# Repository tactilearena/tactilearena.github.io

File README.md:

# TactileArena

**Scalable high-density tactile arenas for measuring ground-contact forces in freely moving animals**
Weiwen Lu\*, Ariel Slepyan\*, Pierce Perkins, Alessandro Ascani Orsini, Kiara Quinn, Nitish V. Thakor (\*equal contribution).
Johns Hopkins University and MIT. Preprint: [bioRxiv](https://www.biorxiv.org/content/10.64898/2026.10.22.760735v1) (2026).

**Website: <https://tactilearena.github.io>** · [Preprint](https://www.biorxiv.org/content/10.64898/2026.10.22.760735v1) · [How it works](https://tactilearena.github.io/how-it-works/) · [Build guide](https://tactilearena.github.io/build/) · [Data](https://tactilearena.github.io/data/)

TactileArena transforms the floor into a sensor. A modular surface of 16,384 pressure-sensitive taxels (2-mm pitch, 512 × 128 mm, nominal 1 kHz) records where, when and with what force a freely moving animal contacts the ground, synchronized with overhead video and without instrumentation of the animal. Each readout board measures 200 of its module's 4,096 taxels per frame and concentrates these measurements on active contacts (adaptive compressive sampling), enabling this combination of sensing area, spatial density and acquisition speed.

The runway is a 64 × 256 piezoresistive array (four 64 × 64 modules, each with its own readout board) under a walking surface, recorded together with an overhead camera and a side camera. This repository holds the readout firmware, the synchronized recording code, the pipeline that takes each recording from raw sensor packets to paw-labeled (FL/FR/HL/HR) stance events and mass-equivalent loading, and the project website (`docs/`).

## Repository layout

```
acquisition/   record_runway.py         four boards + overhead and side cameras on one clock -> .mat + .mp4
               live_view_runway.py      live pressure map (no recording)
               firmware/                readout-board firmware (Teensy 4.1; set BOARD_ID per board)
pipeline/      gait_config.m            paths and study settings (edit this first)
               s1_prepare_recordings.m  background models; video choice and platform corners for new data
               s2_detect_contacts.m     tail-base CNN + contact detector -> pressure movie, contacts
               peak_seed_contact_detector.m  the contact detector (called by s2)
               s3_find_mobile_bouts.m   whole-animal COP trace and walking bouts (+ review window)
               s4_label_paws.m          FL/FR/HL/HR stance events inside the walking bouts (+ labeled video)
               s5_calibrate_to_grams.m  summed taxel response -> mass-equivalent grams
tailbase/      tailbase_cnn.py          tail-base localizer: annotate / train / predict
demo/          run_demo.m               runs the pipeline on the demo recording and checks the result
               expected/                expected walking windows and stance events
data/          tailbase_model/          trained tail-base CNN (best_tail_detector.pt) and its training history
               calibration_0_450/       per-board calibration curves (calibration_0_450.json)
               platform_sheet_template.mat   sensor position relative to the platform corners
hardware/      KiCad sources, fabrication Gerbers and BOM for the 64 x 64 sensor and its readout board (CERN-OHL-P-2.0)
docs/          the website (MkDocs Material; mkdocs.yml at the root, published by .github/workflows/pages.yml)
site_tools/    scripts that produce the website media and the Supplementary Videos (see site_tools/README.md)
```

## Demo

The demo package, `demo_2-24-2026_rat4.zip` (415 MB; 1.36 GB unzipped), is part of the data deposit on Zenodo, [doi:10.5281/zenodo.23286364](https://doi.org/10.5281/zenodo.23286364). It holds one complete recording, rat 4 on 24 Feb 2026 (sciatic nerve pinch group, two weeks before surgery): an 85-s session with five runway crossings. It contains the raw pressure packets (1.0 GB), the overhead video (334 MB) and that recording's annotations, in the same layout as the full data deposit. Extracting it to `C:\` gives `C:\gait_demo\data`.

```matlab
setenv('GAIT_PYTHON', 'C:\path\to\python.exe')   % Python with PyTorch, if not on the PATH
addpath('<repo>/demo')
run_demo('C:\gait_demo\data', 'C:\gait_demo\work')
```

It runs s1 (background model), s2, s3 and s4 and writes to `work/demo_results/`:

- `walking_windows.csv`: the 5 walking windows
- `stance_events.csv`: the 58 labeled stance events (paw, start and end time, position)
- `labeled_walking_windows.mp4`: the overhead camera and pressure map of each walking window, every stance circled and labeled FL/FR/HL/HR (37 MB, about 0.25× real time)

The two tables are compared with `demo/expected/`; a successful run ends with `DEMO PASSED`. Typical run time is about 9 minutes on a desktop workstation (32 logical cores), with or without a GPU: about 6 minutes for the s2 contact detector and 2.5 minutes to render the video.

## Requirements

- **MATLAB** (tested on R2023b) with the Image Processing, Signal Processing, and Statistics and Machine Learning toolboxes.
- **Python 3** for the tail-base CNN: `pip install -r requirements.txt` (tested with Python 3.12, NumPy 2.4, OpenCV 4.13, PyTorch 2.12 CPU and 2.11 CUDA). Install time is a few minutes.
- **A GPU is not needed.** On the demo recording a CPU-only run took the same time and gave the same labeled stance events. Tail-base positions agreed on all but 1 of 1,376 frames, which changed the camera votes of 1 of 197 detector contacts and no label.
- **Disk:** about 60 MB of output per recording, two thirds of it tail-base frame images.
- **Recording only:** the readout boards and firmware (`acquisition/firmware/`), a computer with four USB ports and the two cameras (overhead and side), plus `pyserial` and `scipy`.

## Data

The recordings and the study annotations are on Zenodo, [doi:10.5281/zenodo.23286364](https://doi.org/10.5281/zenodo.23286364) (CC BY 4.0), as one zip per recording (`<M-D-YYYY>_ratN.zip`, 85 files, about 400 MB each) plus `annotations.zip`. Extract all of them into the same folder and point `GAIT_DATA_ROOT` at it:

```
<data_root>/
  <M-D-YYYY>/runway/ratN/runway_tactile_data_*.mat   raw pressure packets (+ camera frame timestamps)
  <M-D-YYYY>/runway/ratN/camera_*.mp4                 overhead video
  annotations/
    recordings.csv               the 85 analyzed recordings (paths relative to data_root)
    homographies/                camera -> sensor projective transform, one per recording
    blind_labels/                manual FL/FR/HL/HR labels (blinded to the algorithm)
    mobile_bout_windows.csv      manually selected walking windows
    cop_trajectory_corrections.csv   keep/trim decisions that produced those windows
    corrected_contacts.csv       manually reviewed contacts over whole recordings, including standing
    mass.csv                     body mass by rat and date
```

## Setup

Set these environment variables before starting MATLAB, or edit the top of `pipeline/gait_config.m`:

| Variable | Meaning |
|---|---|
| `GAIT_DATA_ROOT` | the downloaded data folder above |
| `GAIT_WORK_ROOT` | where outputs are written |
| `GAIT_PYTHON` | Python executable with PyTorch (default `python`) |
| `GAIT_ANNOTATIONS_ROOT` | optional; defaults to `<data_root>/annotations` |

Then add the code to the MATLAB path:

```matlab
addpath('<repo>/pipeline')
```

## Recording

`acquisition/record_runway.py` runs on the acquisition computer (macOS) with the four readout boards connected over USB serial. It sends each board its settings, then releases the board and camera threads from one shared start time, and saves `runway_tactile_data_<time>_M<M>_T<threshold>_D<digipot>.mat` plus one `camera_<K>_<time>.mp4` per camera. The paper's recordings used 90 s, M = 200, threshold 700, digital potentiometer 100, and two cameras at 1920 × 1080 (30 fps target; about 25-27 fps achieved, so use the saved per-frame timestamps). Edit the serial ports and camera indices at the bottom of the script. Each board streams frames at approximately 1 kHz (median interval about 1 ms); see `acquisition/firmware/README.md` for the sampling scheme and packet format. `live_view_runway.py` shows the live pressure map.

## Running the pipeline

Every stage takes an optional list of recordings (`output_name` values from `recordings.csv`) and skips work that already exists.

```matlab
[cfg, R] = gait_config();            % R = recording list with absolute paths
rec = R.output_name(R.rat == 6);     % e.g. one animal

s1_prepare_recordings("backgrounds", rec)  % background image of each overhead video
s2_detect_contacts(rec)                    % ~6 min per recording
s3_find_mobile_bouts("extract", rec)       % COP traces and candidate walking bouts
s4_label_paws(rec)                         % paw-labeled stance events in the walking windows
```

**s1, prepare recordings.** `"backgrounds"` builds the pixel-wise median background image of each overhead video listed in `recordings.csv`; s2 needs it. For a new recording set, `"pick"` chooses the overhead video for each tactile file, `"corners"` asks you to click the four visible platform corners in each video (the sensor corners are inferred from the platform template and a homography is saved), and `"background"` builds the background images and writes a new recording list to `work_root/setup/`.

**s2, detect contacts.** Overhead frames (30 fps) are background-subtracted, warped into the 256 × 64 board space with the body mask, and passed to the tail-base CNN. The detector then reconstructs the 64 × 256 pressure movie from the board packets, segments pressure contacts, and accumulates camera body-quadrant votes (FL/FR/HL/HR) for each contact. Output: `work_root/dynamics/<recording>/`.

**s3, walking bouts.** The whole-animal centre of pressure is computed at ~100 Hz, with each board rendered from its nearest packet by timestamp. Candidate walking bouts are proposed from its speed. `"correct"` opens a review window to keep, reject or trim each candidate; `"stats"` and `"export"` write the per-bout table and the walking windows. The paper used candidates reviewed by hand (the deposit's `mobile_bout_windows.csv`).

An improved automatic detector, `detect_walking_bouts` (actions `"review_auto"` / `"export_auto"`), is included but was **not** used in the paper. It proposes bouts for the same review window. On the 81 labeled recordings, 95% of the 2,469 manually labeled walking prints have their stance midpoint inside one of its proposed bouts. The proposals add time to review: about 1,000 s of proposed bouts against 619 s of manually selected walking windows.

**s4, paw labels.** Inside each walking window, stance contacts are re-segmented from the pressure movie. Each is assigned FL/FR/HL/HR from its position relative to the smoothed whole-animal COP and walking direction, plus 0.3 × log of the camera votes; left/right is decoded in onset order (Viterbi), and back-to-back pieces of one stance are merged. In the manually selected walking windows of 81 recordings, 2,303 of 2,469 manually labeled prints (93.3%) were found and given the correct paw. Output: `work_root/mobile_contacts/<recording>_mobile_contacts.mat`. With `s4_label_paws(rec, struct('video', true))` it also writes `<recording>_paw_labels.mp4`: camera and pressure map for each walking window, every stance labeled, and "human: XX" where a manual label exists and disagrees. These are the final paw labels; s2's provisional labels from camera votes are not used downstream.

**s5, grams.** `s5_calibrate_to_grams(pixel_sum, centroid_x)` converts a summed taxel response with the curve of the board the contact lies on (boards ordered 4-3-2-1 left to right). Values above the calibrated range (~410-421 g) return NaN. See `data/calibration_0_450/README.md`.

## Outputs

Everything is written under `GAIT_WORK_ROOT`. Conventions used by all stages:

- **Time:** seconds on the recording's shared clock, starting at the first pressure sample. Detector times, walking windows and stance events are all on this base.
- **Position:** taxel coordinates on the 64 × 256 runway. `centroid_x` is the column along the runway (1-256; boards 4, 3, 2, 1 from left to right) and `centroid_y` the row across it (1-64). One taxel is 2 mm; COP traces in s3 are already in mm.
- **Pressure:** raw readout counts (12-bit, 0-4095; larger values are readout glitches). Summed responses such as `dynamic_peak_total_pressure` are sums of counts. Convert sums to grams with `s5_calibrate_to_grams`.

| Stage | File (under `GAIT_WORK_ROOT`) | Contents |
|---|---|---|
| s1 | `background_models/<recording>_background_model.mat` | `bg_model`: 1080 × 1920 × 3 uint8 background image (rotated like the analysis frames); `frame_transform`, `source_video`, `n_background_frames` |
| s2 | `dynamics/<recording>/square_tailbase_predictions.csv` | one row per sampled camera frame (30 fps): `frame_index`, `time_s`, `tailbase_x_px`, `tailbase_y_px` (board coordinates, 0-255 × 0-63), `tailbase_confidence` |
| s2 | `dynamics/<recording>/<tactile file>_peak_seed_footstep_dynamics.mat` | the detector output, below |
| s3 | `cop_trajectory/cop_trajectory_raw.mat` | `raw_results`, one element per recording, below |
| s3 | `cop_trajectory/cop_tortuosity_by_bout.csv` | one row per candidate bout: `keep`, `trim_start_idx`/`trim_end_idx` (from the review), `duration_s`, `path_length_mm`, `displacement_mm`, `tortuosity`, `mean_speed_mm_s`, `net_speed_mm_s`, and the same for the video body centroid (`geom_centroid_*`) |
| s3 | `cop_trajectory/mobile_bout_windows.csv` | walking windows: `recording`, `bout_index`, `t_start`, `t_end` |
| s4 | `mobile_contacts/<recording>_mobile_contacts.mat` | `contacts` (the stance events), `bout_windows` (N × 2, s), `info`, below |
| s4 | `mobile_contacts/<recording>_paw_labels.mp4` | labeled video, with `struct('video', true)` |

**s2 detector output** (`*_peak_seed_footstep_dynamics.mat`):

- `pressure_movie_frames`: 64 × 256 × T uint16, the reconstructed pressure movie (about 120 frames per second).
- `pressure_movie_times`: T × 1, the time of each frame.
- `footstep_events`: the detector's contacts. Fields used downstream are:
  - `start_time`, `end_time`, `duration`, `start_frame`, `end_frame`
  - `centroid_x`, `centroid_y`
  - `quad_votes`: 1 × 4 camera body-quadrant votes for FL, FR, HL, HR
  - `label`: provisional, FL/FR/HL/HR or `noise`; superseded by s4
  - `valid_stance`
  - `dynamic_roi`: crop box `x1`, `x2`, `y1`, `y2`
  - `roi_frames`: the pressure crop over the stance
  - `dynamic_peak_total_pressure`
- `body_axis_trace`: the camera-derived body axis over time (`time`, body centroid `cx`, `cy`, unit vectors `head_ax_*` and `right_ax_*`, `reliable`).
- `clean_gait_events`, `export_params`, `export_source`: bookkeeping and the detector settings used.

**s3 COP trace** (`raw_results`): one element per recording, with:

- the recording's metadata
- `t` (s, ~100 Hz) and `source_t`
- `cop_x_mm`, `cop_y_mm`: smoothed whole-animal COP (`raw_cop_*` unsmoothed)
- `geom_centroid_*`: the unweighted centroid of the active taxels
- `total_pressure`, `n_active_px`, `velocity_mm_s`
- `is_moving`, `bout_starts`, `bout_ends`: candidate bouts, as indices into `t`

**s4 stance events** (`contacts`): one element per contact, sorted by start time. Use the ones with `mobile_valid = true`; contacts with `mobile_duplicate = true` are fragments of another stance. Per stance event:

| Field | Meaning |
|---|---|
| `label` | FL, FR, HL or HR (final) |
| `start_time`, `end_time`, `duration` | stance timing (s) |
| `start_frame`, `end_frame` | frame indices into `pressure_movie_frames` |
| `centroid_x`, `centroid_y` | contact position (taxels) |
| `dynamic_peak_total_pressure` | peak summed response during stance (counts) |
| `bout_index` | row of `bout_windows` the stance lies in |
| `mobile_margin` | assignment confidence: the smaller of the \|log-odds\| for left vs right and for fore vs hind (0 = coin flip) |
| `quad_votes` | camera votes borrowed from the nearest s2 contact |
| `track` | the frame-by-frame track behind the contact |

`demo/run_demo.m` shows how to turn the valid contacts into a simple table (`stance_events.csv`).

## License and citation

Code: MIT License; see [LICENSE](LICENSE). Hardware design files in `hardware/`: CERN-OHL-P-2.0; see [LICENSE-hardware](LICENSE-hardware). Website text, figures and media in `docs/`: CC BY 4.0; see [LICENSE-docs](LICENSE-docs). The recordings are released separately under CC BY 4.0.

Scripts used to compute the gait metrics and statistical analyses reported in the manuscript are available from the corresponding authors upon request.

If you use this code or data, please cite the preprint: Lu, W., Slepyan, A. et al. Scalable high-density tactile arenas for measuring ground-contact forces in freely moving animals. bioRxiv (2026), [doi:10.64898/2026.10.22.760735](https://www.biorxiv.org/content/10.64898/2026.10.22.760735v1). See also [CITATION.cff](CITATION.cff).

This repository started as [victorlu2220/Gait-Project-Pipeline](https://github.com/victorlu2220/Gait-Project-Pipeline); its history is preserved here.

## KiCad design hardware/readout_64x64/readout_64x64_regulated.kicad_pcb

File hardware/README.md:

# TactileArena hardware

Design files for one TactileArena module: a 64 × 64-taxel flexible-PCB sensor and its readout board. A runway uses
four of each (16,384 taxels, 512 × 128 mm). Licensed under the
[CERN Open Hardware Licence v2, Permissive](../LICENSE-hardware) (CERN-OHL-P-2.0).

| Folder | Contents |
|---|---|
| [`sensor_64x64/`](sensor_64x64) | KiCad layout (`MD_sensor_64x64.kicad_pcb`; layout only, no components) and the Gerbers used for fabrication (`gerbers/MD_sensor_64x64_gerbers.zip`) |
| [`readout_64x64/`](readout_64x64) | KiCad schematic and layout (`readout_64x64_regulated.*`), Gerbers and drill files (`gerbers/readout_64x64_regulated_gerbers.zip`), JLCPCB assembly files ([`jlcpcb/`](readout_64x64/jlcpcb): BOM and placement) and the bill of materials ([`bom.csv`](readout_64x64/bom.csv)) |

The sensor Gerber zip is the file the sensors were made from; its copper layers and board outline match the KiCad
layout (checked layer by layer). The readout-board Gerbers and assembly files are exported from the KiCad layout
in this folder with the Fabrication Toolkit plugin (KiCad 10).

## Sensor module (`sensor_64x64`)

- **What it is:** a 64 × 64 grid of electrode pairs at 2 mm pitch (128 × 128 mm active area) with
  row and column traces routed to two 70-contact, 0.5 mm-pitch tails. There are no components on it. A
  piezoresistive film (Velostat/Linqstat) laid over the grid makes each electrode pair a pressure-sensitive taxel.
- **Fabrication:** 2-layer flexible PCB (FPC). The board setup in KiCad retains the default FR4 stackup, which does not apply.
- **Outline:** 157.9 × 179.7 mm (chamfered body plus the two tails). Traces are 0.2 mm; most vias are 0.4 mm pad /
  0.2 mm drill.
- **Tails:** each tail connects to one Molex 505110 connector on the readout board. A stiffener under the tail
  contacts should bring their thickness to the value specified for the connector (Molex 505110 datasheet).

## Readout board (`readout_64x64`)

- **What it does:** shift registers (74LVC595) drive the 64 rows, two 32:1 multiplexers (ADG732) select a column in
  each half of the sensor, and two 12-bit ADCs (AD7476) read them over SPI. Two digital potentiometers
  (MCP41HV51) set the gain. A Teensy 4.1 runs the [adaptive sampling firmware](../acquisition/firmware) and
  streams to the computer over USB.
- **PCB:** 4 layers, 1.6 mm, 91.9 × 56.3 mm, all parts on the top side. The smallest vias are 0.35 mm pad /
  0.15 mm drill; these should be confirmed against the capabilities of the fabrication service.
- **Parts:** [`bom.csv`](readout_64x64/bom.csv), per board. All parts except the Teensy 4.1 can be placed by the
  board house; [`jlcpcb/`](readout_64x64/jlcpcb) contains the JLCPCB BOM and placement files. The Teensy 4.1 is
  marked do-not-populate and is soldered by hand. Parts that are out of stock at JLCPCB when ordering can be sourced
  through its parts pre-order or global sourcing services, or soldered by hand.
- **Soldering:** the multiplexers (TQFP-48), shift registers (TSSOP-16) and the two 70-pin connectors are 0.5–0.65 mm
  pitch; a solder-paste stencil with a hot plate or reflow oven is recommended. The Teensy is mounted on 2 × 24 pin
  headers.
- **3D models** are not included; some footprints reference local model files, so these parts appear without bodies
  in the KiCad 3D viewer.

## Building a runway

A runway requires four sensor modules, four readout boards, piezoresistive film, a waterproof cloth and an enclosure.
The [Build guide](https://tactilearena.github.io/build/) describes the parts cost (approximately US$550 per runway),
the assembly procedure and video, firmware installation (`BOARD_ID` 1–4) and recording.

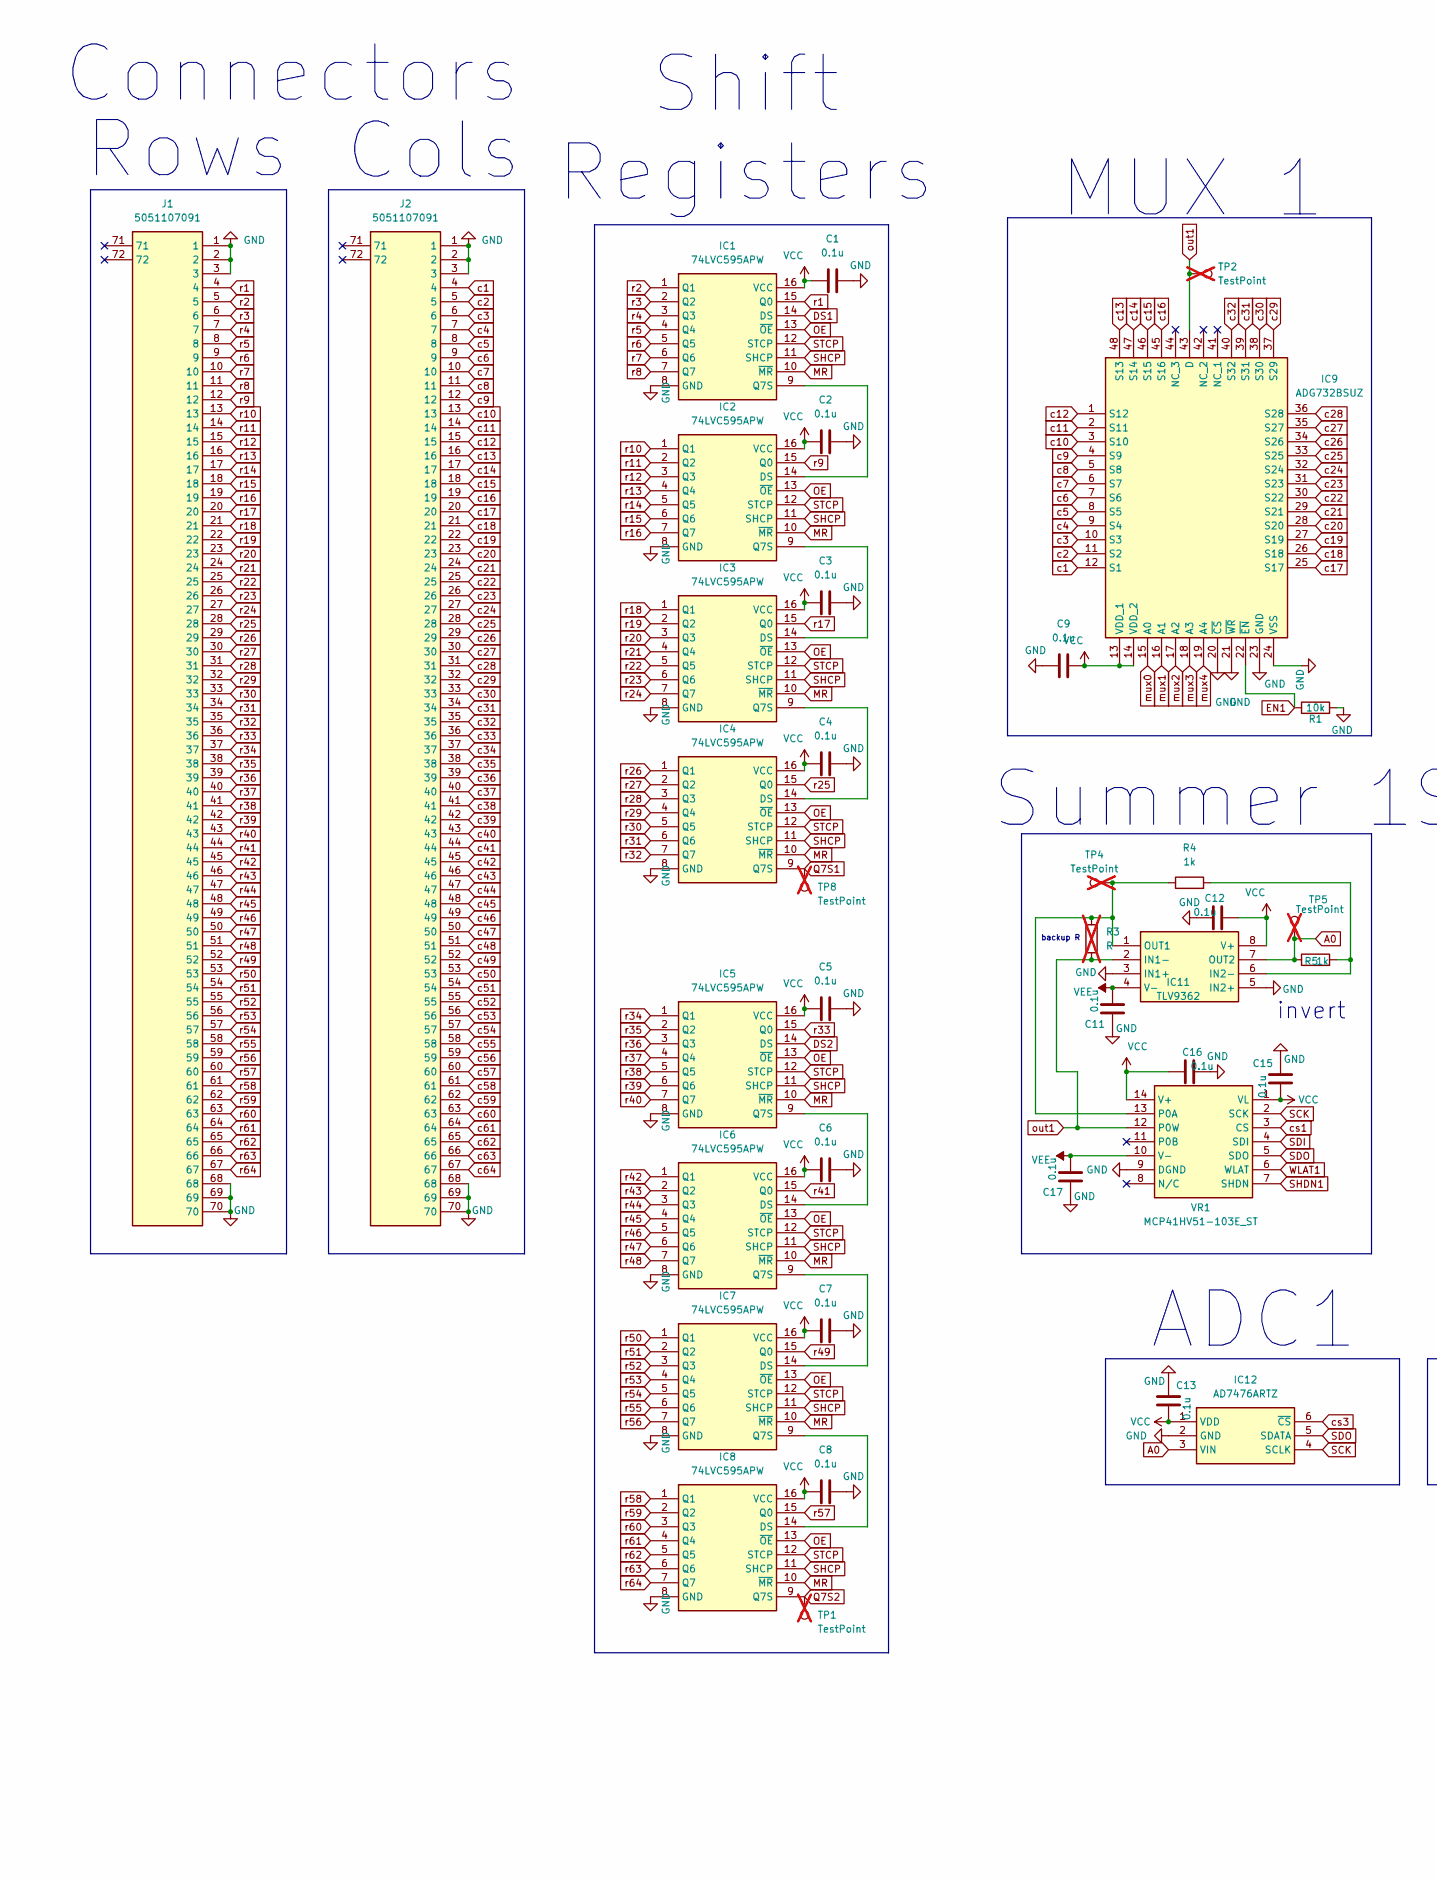
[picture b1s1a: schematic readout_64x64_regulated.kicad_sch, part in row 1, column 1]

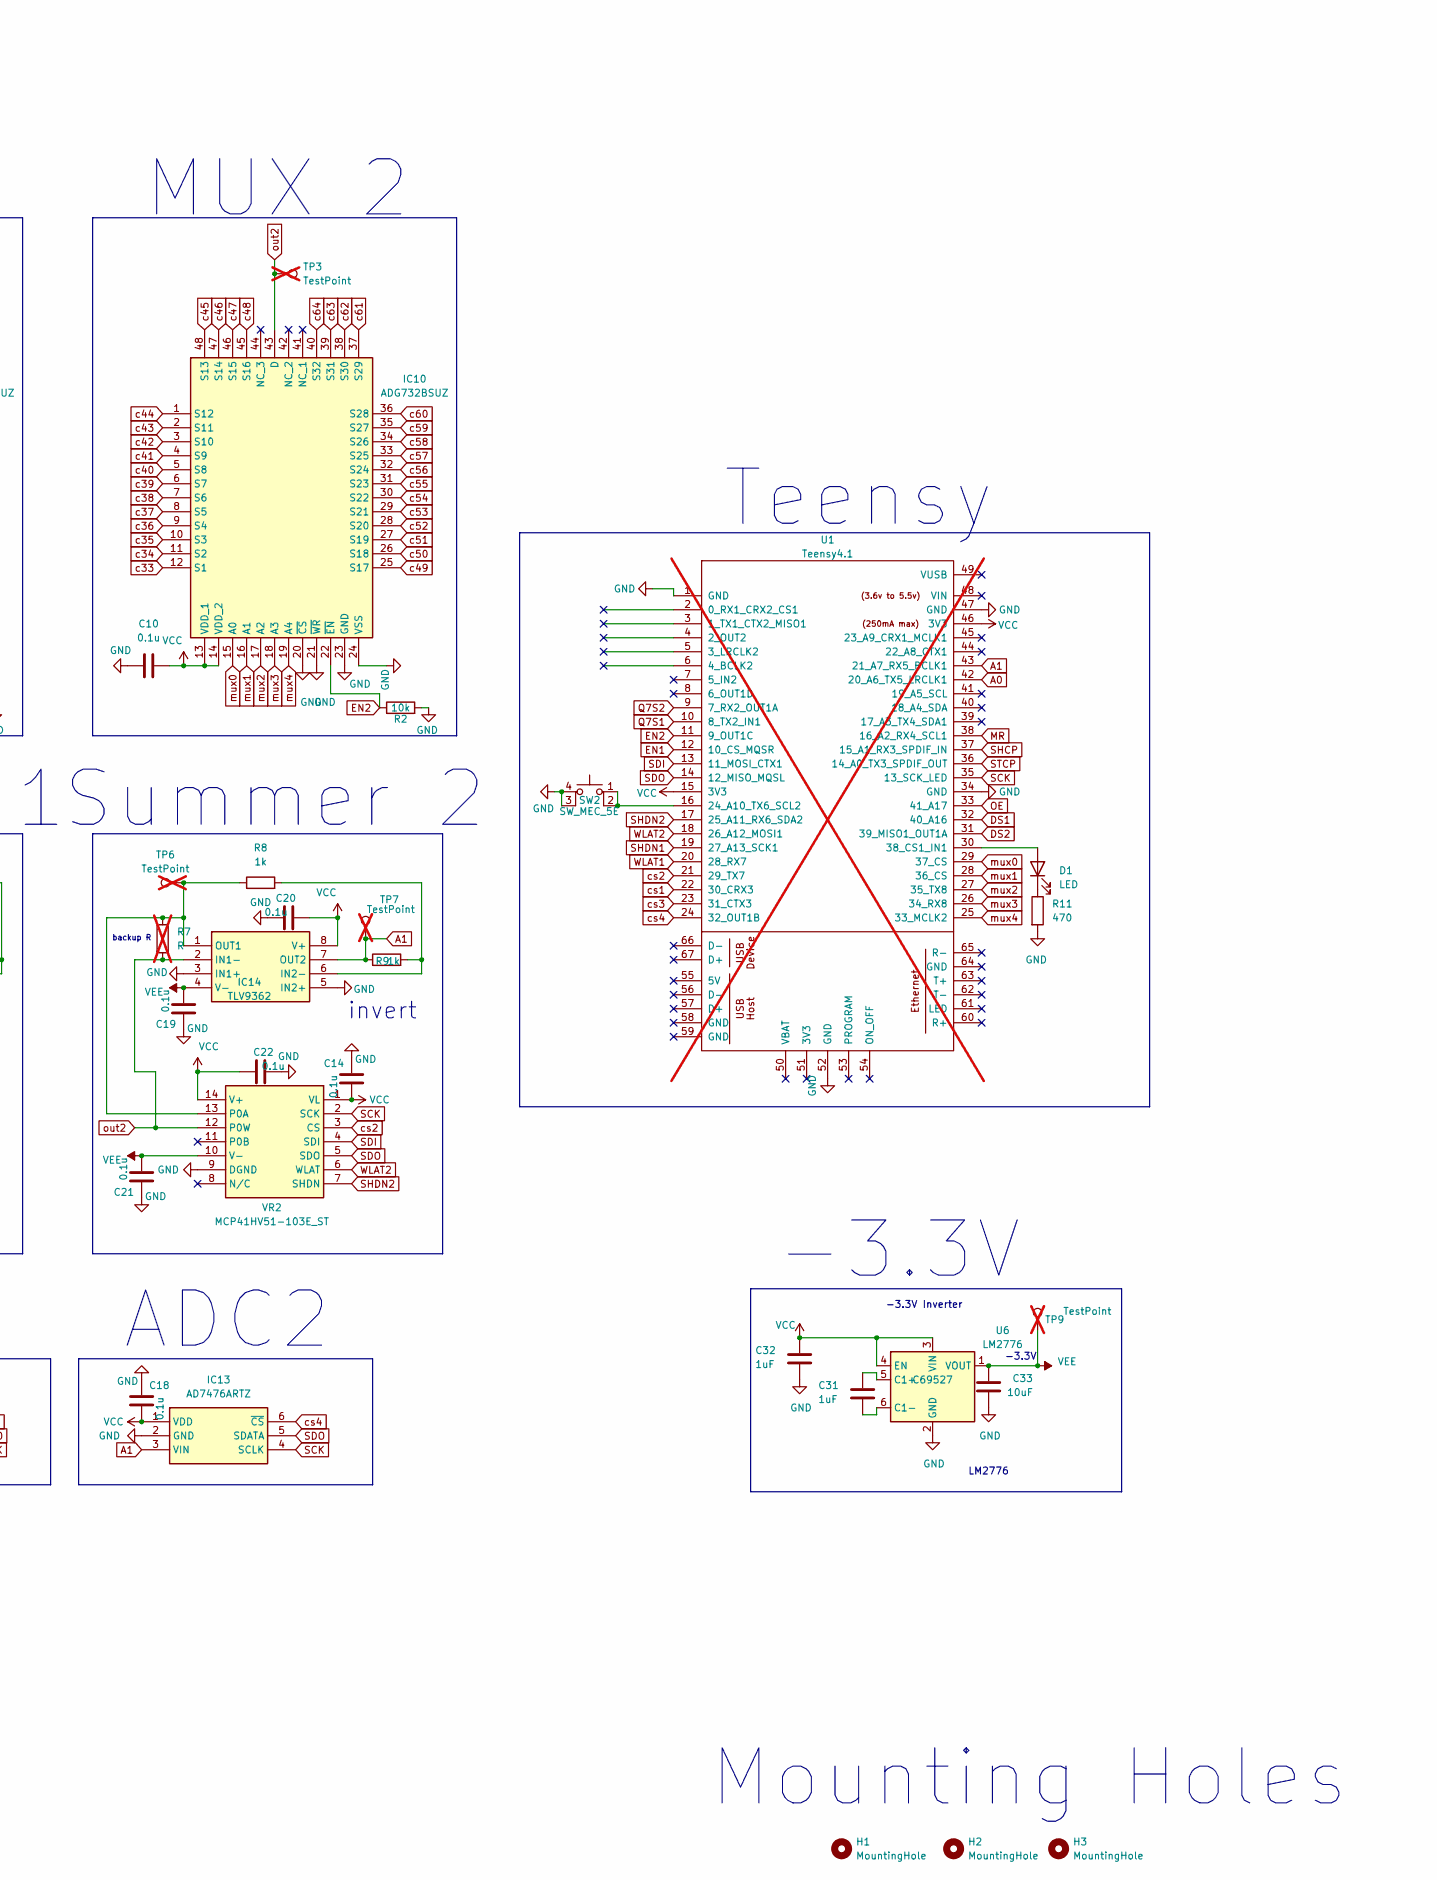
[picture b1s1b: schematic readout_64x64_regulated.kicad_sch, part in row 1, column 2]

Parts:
C1, C2, C3, C4, C5, C6, C7, C8, C9, C10, C11, C12, C13, C14, C15, C16, C17, C18, C19, C20, C21, C22: 0.1u; C_0805_2012Metric; LCSC Part # C28233
C31, C32: 1uF; C_0805_2012Metric; LCSC Part # C28323
C33: 10uF; C_0805_2012Metric; LCSC Part # C15850
D1: LED; LED_0805_2012Metric; LCSC Part # C2297
H1, H2, H3: MountingHole; MountingHole_3.2mm_M3
IC1, IC2, IC3, IC4, IC5, IC6, IC7, IC8: 74LVC595APW; SOP65P640X110-16N; Manufacturer_Part_Number 74LVC595APW; Mouser Part Number 771-74LVC595APW
IC9, IC10: ADG732BSUZ; QFP50P900X900X120-48N; Manufacturer_Part_Number ADG732BSUZ; Mouser Part Number 584-ADG732BSUZ
IC11, IC14: TLV9362; SOIC127P600X175-8N; Manufacturer_Part_Number LM358BAIDR; Mouser Part Number 595-LM358BAIDR
IC12, IC13: AD7476ARTZ; SOT95P280X145-6N; Manufacturer_Part_Number AD7476ARTZ; LCSC Part # C651070
J1, J2: 5051107091; Manufacturer_Part_Number 5051107091; LCSC Part # C6393753
R1, R2: 10k; R_0805_2012Metric; LCSC Part # C17414
R3, R7: R; R_0805_2012Metric; not fitted
R4, R5, R8, R9: 1k; R_0805_2012Metric; LCSC Part # C17513
R11: 470; R_0805_2012Metric; LCSC Part # C17710
SW2: SW_MEC_5E; PTS647SN50SMTR2LFS; Manufacturer_Part_Number TS4538TP; LCSC Part # C398052
TP1, TP2, TP3, TP4, TP5, TP6, TP7, TP8, TP9: TestPoint; TestPoint_Pad_1.0x1.0mm; not fitted
U1: Teensy4.1; Teensy41; not fitted
U6: LM2776; SOT-23-6; LCSC Part # C69527
VR1, VR2: MCP41HV51-103E_ST; SOP65P640X120-14N; Manufacturer_Part_Number MCP41HV51-103E/ST; Mouser Part Number 579-MCP41HV51-103EST

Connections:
A0: IC11.7 (OUT2), IC12.3 (VIN), R5.1, TP5.1, U1.42 (20_A6_TX5_LRCLK1)
A1: IC13.3 (VIN), IC14.7 (OUT2), R9.1, TP7.1, U1.43 (21_A7_RX5_BCLK1)
DS1: IC1.14 (DS), U1.32 (40_A16)
DS2: IC5.14 (DS), U1.31 (39_MISO1_OUT1A)
EN1: IC9.22 (~EN), R1.1, U1.12 (10_CS_MQSR)
EN2: IC10.22 (~EN), R2.1, U1.11 (9_OUT1C)
GND: C1.2, C2.2, C3.2, C4.2, C5.2, C6.2, C7.2, C8.2, C9.2, C10.2, C11.2, C12.2, C13.2, C14.2, C15.2, C16.2, C17.2, C18.2, C19.2, C20.2, C21.2, C22.2, C32.2, C33.2, IC1.8 (GND), IC2.8 (GND), IC3.8 (GND), IC4.8 (GND), IC5.8 (GND), IC6.8 (GND), IC7.8 (GND), IC8.8 (GND), IC9.20 (~CS), IC9.21 (~WR), IC9.23 (GND), IC9.24 (VSS), IC10.20 (~CS), IC10.21 (~WR), IC10.23 (GND), IC10.24 (VSS), IC11.3 (IN1+), IC11.5 (IN2+), IC12.2 (GND), IC13.2 (GND), IC14.3 (IN1+), IC14.5 (IN2+), J1.1, J1.2, J1.3, J1.68, J1.69, J1.70, J2.1, J2.2, J2.3, J2.68, J2.69, J2.70, R1.2, R2.2, R11.2, SW2.3 (K), SW2.4 (A), U1.1 (GND), U1.34 (GND), U1.47 (GND), U1.52 (GND), U6.2 (GND), VR1.9 (DGND), VR2.9 (DGND)
MR: IC1.10 (~MR), IC2.10 (~MR), IC3.10 (~MR), IC4.10 (~MR), IC5.10 (~MR), IC6.10 (~MR), IC7.10 (~MR), IC8.10 (~MR), U1.38 (16_A2_RX4_SCL1)
unnamed: D1.2 (A), U1.30 (38_CS1_IN1)
unnamed: D1.1 (K), R11.1
unnamed: IC1.9 (Q7S), IC2.14 (DS)
unnamed: IC2.9 (Q7S), IC3.14 (DS)
unnamed: IC3.9 (Q7S), IC4.14 (DS)
unnamed: IC5.9 (Q7S), IC6.14 (DS)
unnamed: IC6.9 (Q7S), IC7.14 (DS)
unnamed: IC7.9 (Q7S), IC8.14 (DS)
unnamed: IC11.6 (IN2-), R4.2, R5.2
unnamed: IC11.1 (OUT1), R3.2, R4.1, TP4.1, VR1.13 (P0A)
unnamed: IC14.6 (IN2-), R8.2, R9.2
unnamed: IC14.1 (OUT1), R7.2, R8.1, TP6.1, VR2.13 (P0A)
unnamed: SW2.1, SW2.2, U1.16 (24_A10_TX6_SCL2)
unnamed: C31.1, U6.5 (C1+)
unnamed: C31.2, U6.6 (C1-)
OE: IC1.13 (~OE), IC2.13 (~OE), IC3.13 (~OE), IC4.13 (~OE), IC5.13 (~OE), IC6.13 (~OE), IC7.13 (~OE), IC8.13 (~OE), U1.33 (41_A17)
Q7S1: IC4.9 (Q7S), TP8.1, U1.10 (8_TX2_IN1)
Q7S2: IC8.9 (Q7S), TP1.1, U1.9 (7_RX2_OUT1A)
SCK: IC12.4 (SCLK), IC13.4 (SCLK), U1.35 (13_SCK_LED), VR1.2 (SCK), VR2.2 (SCK)
SDI: U1.13 (11_MOSI_CTX1), VR1.4 (SDI), VR2.4 (SDI)
SDO: IC12.5 (SDATA), IC13.5 (SDATA), U1.14 (12_MISO_MQSL), VR1.5 (SDO), VR2.5 (SDO)
SHCP: IC1.11 (SHCP), IC2.11 (SHCP), IC3.11 (SHCP), IC4.11 (SHCP), IC5.11 (SHCP), IC6.11 (SHCP), IC7.11 (SHCP), IC8.11 (SHCP), U1.37 (15_A1_RX3_SPDIF_IN)
SHDN1: U1.19 (27_A13_SCK1), VR1.7 (SHDN)
SHDN2: U1.17 (25_A11_RX6_SDA2), VR2.7 (SHDN)
STCP: IC1.12 (STCP), IC2.12 (STCP), IC3.12 (STCP), IC4.12 (STCP), IC5.12 (STCP), IC6.12 (STCP), IC7.12 (STCP), IC8.12 (STCP), U1.36 (14_A0_TX3_SPDIF_OUT)
VCC: C1.1, C2.1, C3.1, C4.1, C5.1, C6.1, C7.1, C8.1, C9.1, C10.1, C12.1, C13.1, C14.1, C15.1, C16.1, C18.1, C20.1, C22.1, C32.1, IC1.16 (VCC), IC2.16 (VCC), IC3.16 (VCC), IC4.16 (VCC), IC5.16 (VCC), IC6.16 (VCC), IC7.16 (VCC), IC8.16 (VCC), IC9.13 (VDD_1), IC9.14 (VDD_2), IC10.13 (VDD_1), IC10.14 (VDD_2), IC11.8 (V+), IC12.1 (VDD), IC13.1 (VDD), IC14.8 (V+), U1.15 (3V3), U1.46 (3V3), U6.3 (VIN), U6.4 (EN), VR1.1 (VL), VR1.14 (V+), VR2.1 (VL), VR2.14 (V+)
VEE: C11.1, C17.1, C19.1, C21.1, C33.1, IC11.4 (V-), IC14.4 (V-), TP9.1, U6.1 (VOUT), VR1.10 (V-), VR2.10 (V-)
WLAT1: U1.20 (28_RX7), VR1.6 (WLAT)
WLAT2: U1.18 (26_A12_MOSI1), VR2.6 (WLAT)
c1: IC9.12 (S1), J2.4
c2: IC9.11 (S2), J2.5
c3: IC9.10 (S3), J2.6
c4: IC9.9 (S4), J2.7
c5: IC9.8 (S5), J2.8
c6: IC9.7 (S6), J2.9
c7: IC9.6 (S7), J2.10
c8: IC9.5 (S8), J2.11
c9: IC9.4 (S9), J2.12
c10: IC9.3 (S10), J2.13
c11: IC9.2 (S11), J2.14
c12: IC9.1 (S12), J2.15
c13: IC9.48 (S13), J2.16
c14: IC9.47 (S14), J2.17
c15: IC9.46 (S15), J2.18
c16: IC9.45 (S16), J2.19
c17: IC9.25 (S17), J2.20
c18: IC9.26 (S18), J2.21
c19: IC9.27 (S19), J2.22
c20: IC9.28 (S20), J2.23
c21: IC9.29 (S21), J2.24
c22: IC9.30 (S22), J2.25
c23: IC9.31 (S23), J2.26
c24: IC9.32 (S24), J2.27
c25: IC9.33 (S25), J2.28
c26: IC9.34 (S26), J2.29
c27: IC9.35 (S27), J2.30
c28: IC9.36 (S28), J2.31
c29: IC9.37 (S29), J2.32
c30: IC9.38 (S30), J2.33
c31: IC9.39 (S31), J2.34
c32: IC9.40 (S32), J2.35
c33: IC10.12 (S1), J2.36
c34: IC10.11 (S2), J2.37
c35: IC10.10 (S3), J2.38
c36: IC10.9 (S4), J2.39
c37: IC10.8 (S5), J2.40
c38: IC10.7 (S6), J2.41
c39: IC10.6 (S7), J2.42
c40: IC10.5 (S8), J2.43
c41: IC10.4 (S9), J2.44
c42: IC10.3 (S10), J2.45
c43: IC10.2 (S11), J2.46
c44: IC10.1 (S12), J2.47
c45: IC10.48 (S13), J2.48
c46: IC10.47 (S14), J2.49
c47: IC10.46 (S15), J2.50
c48: IC10.45 (S16), J2.51
c49: IC10.25 (S17), J2.52
c50: IC10.26 (S18), J2.53
c51: IC10.27 (S19), J2.54
c52: IC10.28 (S20), J2.55
c53: IC10.29 (S21), J2.56
c54: IC10.30 (S22), J2.57
c55: IC10.31 (S23), J2.58
c56: IC10.32 (S24), J2.59
c57: IC10.33 (S25), J2.60
c58: IC10.34 (S26), J2.61
c59: IC10.35 (S27), J2.62
c60: IC10.36 (S28), J2.63
c61: IC10.37 (S29), J2.64
c62: IC10.38 (S30), J2.65
c63: IC10.39 (S31), J2.66
c64: IC10.40 (S32), J2.67
cs1: U1.22 (30_CRX3), VR1.3 (CS)
cs2: U1.21 (29_TX7), VR2.3 (CS)
cs3: IC12.6 (~CS), U1.23 (31_CTX3)
cs4: IC13.6 (~CS), U1.24 (32_OUT1B)
mux0: IC9.15 (A0), IC10.15 (A0), U1.29 (37_CS)
mux1: IC9.16 (A1), IC10.16 (A1), U1.28 (36_CS)
mux2: IC9.17 (A2), IC10.17 (A2), U1.27 (35_TX8)
mux3: IC9.18 (A3), IC10.18 (A3), U1.26 (34_RX8)
mux4: IC9.19 (A4), IC10.19 (A4), U1.25 (33_MCLK2)
out1: IC9.43 (D), IC11.2 (IN1-), R3.1, TP2.1, VR1.12 (P0W)
out2: IC10.43 (D), IC14.2 (IN1-), R7.1, TP3.1, VR2.12 (P0W)
r1: IC1.15 (Q0), J1.4
r2: IC1.1 (Q1), J1.5
r3: IC1.2 (Q2), J1.6
r4: IC1.3 (Q3), J1.7
r5: IC1.4 (Q4), J1.8
r6: IC1.5 (Q5), J1.9
r7: IC1.6 (Q6), J1.10
r8: IC1.7 (Q7), J1.11
r9: IC2.15 (Q0), J1.12
r10: IC2.1 (Q1), J1.13
r11: IC2.2 (Q2), J1.14
r12: IC2.3 (Q3), J1.15
r13: IC2.4 (Q4), J1.16
r14: IC2.5 (Q5), J1.17
r15: IC2.6 (Q6), J1.18
r16: IC2.7 (Q7), J1.19
r17: IC3.15 (Q0), J1.20
r18: IC3.1 (Q1), J1.21
r19: IC3.2 (Q2), J1.22
r20: IC3.3 (Q3), J1.23
r21: IC3.4 (Q4), J1.24
r22: IC3.5 (Q5), J1.25
r23: IC3.6 (Q6), J1.26
r24: IC3.7 (Q7), J1.27
r25: IC4.15 (Q0), J1.28
r26: IC4.1 (Q1), J1.29
r27: IC4.2 (Q2), J1.30
r28: IC4.3 (Q3), J1.31
r29: IC4.4 (Q4), J1.32
r30: IC4.5 (Q5), J1.33
r31: IC4.6 (Q6), J1.34
r32: IC4.7 (Q7), J1.35
r33: IC5.15 (Q0), J1.36
r34: IC5.1 (Q1), J1.37
r35: IC5.2 (Q2), J1.38
r36: IC5.3 (Q3), J1.39
r37: IC5.4 (Q4), J1.40
r38: IC5.5 (Q5), J1.41
r39: IC5.6 (Q6), J1.42
r40: IC5.7 (Q7), J1.43
r41: IC6.15 (Q0), J1.44
r42: IC6.1 (Q1), J1.45
r43: IC6.2 (Q2), J1.46
r44: IC6.3 (Q3), J1.47
r45: IC6.4 (Q4), J1.48
r46: IC6.5 (Q5), J1.49
r47: IC6.6 (Q6), J1.50
r48: IC6.7 (Q7), J1.51
r49: IC7.15 (Q0), J1.52
r50: IC7.1 (Q1), J1.53
r51: IC7.2 (Q2), J1.54
r52: IC7.3 (Q3), J1.55
r53: IC7.4 (Q4), J1.56
r54: IC7.5 (Q5), J1.57
r55: IC7.6 (Q6), J1.58
r56: IC7.7 (Q7), J1.59
r57: IC8.15 (Q0), J1.60
r58: IC8.1 (Q1), J1.61
r59: IC8.2 (Q2), J1.62
r60: IC8.3 (Q3), J1.63
r61: IC8.4 (Q4), J1.64
r62: IC8.5 (Q5), J1.65
r63: IC8.6 (Q6), J1.66
r64: IC8.7 (Q7), J1.67

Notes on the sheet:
invert
Shift Registers
backup R
Connectors
Rows
Teensy
Summer 1
-3.3V
ADC1
Cols
ADC2
MUX 2
-3.3V Inverter
LM2776
Summer 2
MUX 1
Mounting Holes

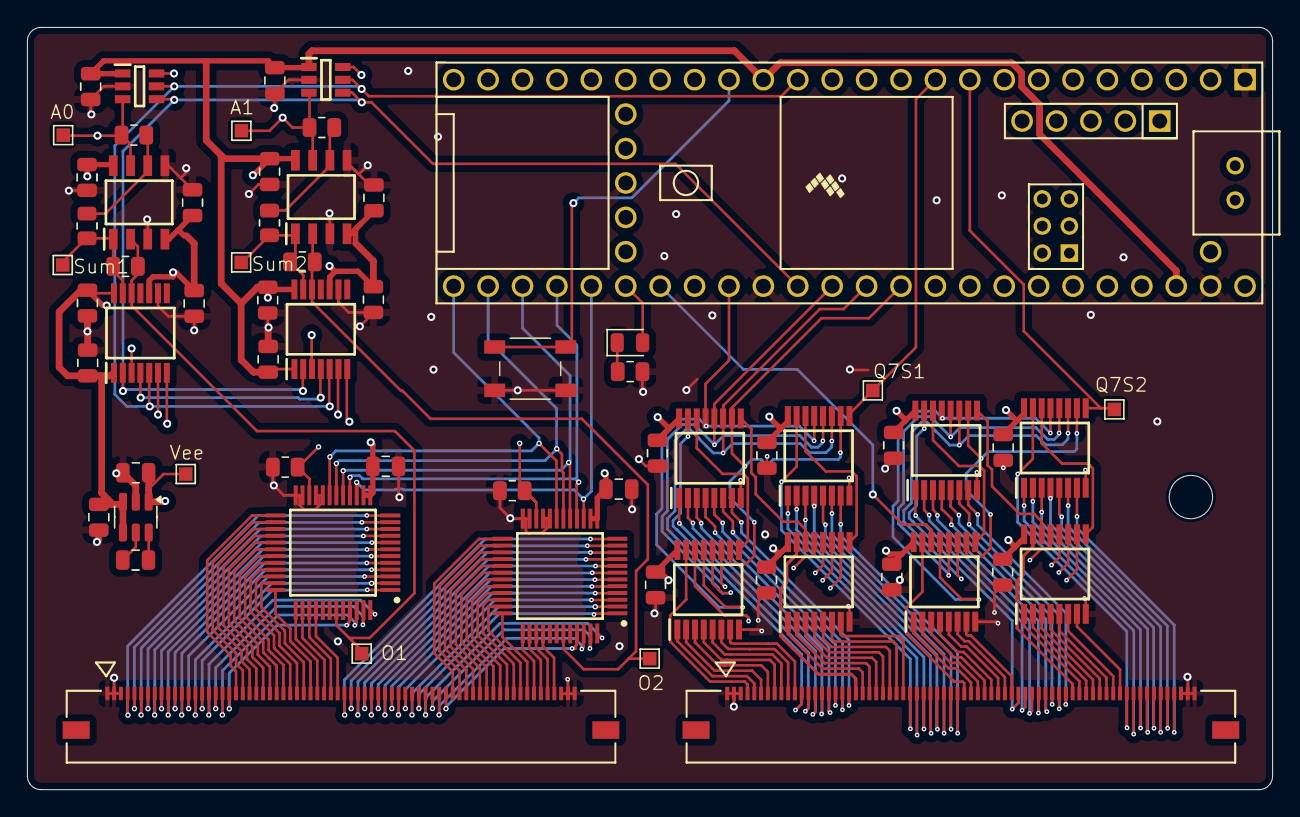
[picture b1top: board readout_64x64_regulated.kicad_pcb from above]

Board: 4 copper layers, 91.9 x 56.3 mm, 66 parts (0 on the bottom side), 176 nets.

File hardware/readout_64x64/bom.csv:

Reference,Qty per board,Value,Description,Manufacturer part number,LCSC,Footprint,Fit,Notes
IC1-IC8,8,74LVC595APW,8-bit shift register (drives the sensor rows),74LVC595APW,C426713,SOP65P640X110-16N (TSSOP-16),SMT,
IC9 IC10,2,ADG732BSUZ,32:1 analog multiplexer (selects the sensor column),ADG732BSUZ,C579103,QFP50P900X900X120-48N (TQFP-48),SMT,0.5 mm pitch
IC11 IC14,2,TLV9362,Dual op-amp,TLV9362IDR,C4367884,SOIC127P600X175-8N (SOIC-8),SMT,The schematic's Manufacturer_Part_Number field still reads LM358BAIDR; the fitted part is TLV9362 (value and LCSC fields)
IC12 IC13,2,AD7476ARTZ,12-bit ADC (SPI),AD7476ARTZ,C651070,SOT95P280X145-6N (SOT-23-6),SMT,
J1 J2,2,5051107091,70-pin 0.5 mm FPC connector for the sensor's two tails,Molex 505110-7091,C6393753,5051107091,SMT,0.5 mm pitch
U6,1,LM2776,Switched-capacitor voltage inverter,LM2776DBVR,C69527,SOT-23-6,SMT,
VR1 VR2,2,MCP41HV51-103E/ST,10 kOhm digital potentiometer (gain; set by the firmware's digipot value),MCP41HV51-103E/ST,C637062,SOP65P640X120-14N (TSSOP-14),SMT,Required
U1,1,Teensy 4.1,Microcontroller board,Teensy 4.1 (PJRC/SparkFun DEV-16771),,Teensy41,Hand,Marked DNP in the schematic; solder on 2 x 24 pin headers
C1-C22,22,0.1 uF,Ceramic capacitor,,C28233,0805,SMT,
C31 C32,2,1 uF,Ceramic capacitor,,C28323,0805,SMT,
C33,1,10 uF,Ceramic capacitor,,C15850,0805,SMT,
D1,1,LED,Indicator LED,,C2297,0805,SMT,
R1 R2,2,10k,Resistor,,C17414,0805,SMT,
R4 R5 R8 R9,4,1k,Resistor,,C17513,0805,SMT,
R11,1,470,Resistor,,C17710,0805,SMT,
SW2,1,SW_MEC_5E,Tactile switch (spare user button on Teensy pin 24; not used by the firmware),SHOU HAN TS4538TP (4.5 x 4.5 x 3.8 mm),C398052,PTS647SN50SMTR2LFS,SMT,Fits the PTS647 footprint
R3 R7,2,R,Not fitted,,,0805,DNP,
TP1-TP9,9,TestPoint,Test pads,,,TestPoint_Pad_1.0x1.0mm,DNP,Bare pads; nothing to fit

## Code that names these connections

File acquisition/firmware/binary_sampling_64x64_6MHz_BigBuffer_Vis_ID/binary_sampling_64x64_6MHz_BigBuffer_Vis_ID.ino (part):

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
// Shift register pins
#define MR 16
#define SHCP 15
#define STCP 14
#define OE 41
#define DS1 40  // Input to shift registers controlling rows 0-31
#define DS2 39  // Input to shift registers controlling rows 32-63
#define Q7S1 8  // Output from last shift register in chain 1
#define Q7S2 7  // Output from last shift register in chain 2

// Mux pins
#define MUX0 37
#define MUX1 36
#define MUX2 35
#define MUX3 34
#define MUX4 33

// Mux enables
#define EN1 10  // Enable for mux handling columns 0-31
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#define CS4 32  // SPI ADC2 (columns 32-63)

// Potentiometer pins
#define SHDN1 27
#define WLAT1 28
#define SHDN2 25
#define WLAT2 26

// LED pin
#define LEDpin 38
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void setup() {
  Serial.begin(0);  // Full USB speed

  pinMode(STCP, OUTPUT);
  pinMode(DS1, OUTPUT);
  pinMode(DS2, OUTPUT);
  pinMode(SHCP, OUTPUT);
  pinMode(OE, OUTPUT);
  pinMode(MR, OUTPUT);

  initializeShiftRegisters();
  digitalWriteFast(OE, LOW);

  pinMode(MUX0, OUTPUT);
  pinMode(MUX1, OUTPUT);
  pinMode(MUX2, OUTPUT);
  pinMode(MUX3, OUTPUT);
  pinMode(MUX4, OUTPUT);

  pinMode(EN1, OUTPUT);
  pinMode(EN2, OUTPUT);
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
